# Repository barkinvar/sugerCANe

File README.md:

# sugarCANe — sensor inputs over CAN

[GitHub repository: barkinvar/sugerCANe](https://github.com/barkinvar/sugerCANe)

A compact interface for **three NPN, PNP or logic sensors** on an FRC robot. Each port has a removable **5 V / 12 V power jumper**; input type is configured in software. CAN provides sensor readings, device-ID changes and recoverable firmware updates.

**sugarCANe** is the product name; SC12 Rev H remains the hardware identity. A tiny pixel-cane island sits on the front, below the upper-left mounting hole and above the large capacitor. A vertical pixel wordmark reads bottom to top beside C1. The underside has 79 SMT parts, a small wordmark and TERM/GND service labels. [Front render](current/output/review/board_top.png) · [bottom render](current/output/review/board_bottom.png).

**Isolated compact layout branch (`codex/compact-board`); power transient screening passes; factory qualification remains pending.**

**Start with [Rev H in `current/`](current/README.md).** It is an unbuilt engineering prototype, with [physical qualification still pending](current/docs/VALIDATION.md). It uses its own protocol and drivers; it is not compatible with CTRE Phoenix or GrappleHook.

Rev H adds one RGB status LED on the right, with space for a printed light duct, and a recessed female programming socket for small batches. It retains G's protected sensor supplies, CAN fault reset and rail measurements. See [the engineering review](current/docs/ORDER_READINESS.md) for the evidence and remaining physical tests.

**Selected assembly plan:** JLC fits **129 SMT parts (50 top / 79 bottom)**. You buy **STM32F042K6T6 from DigiKey** and solder U5, then fit ten through-hole parts and three jumper caps. U5 is omitted from the factory BOM, CPL and stencil. The retained dated sourcing snapshot lists stock for ten boards for all 54 factory types; power transient screening passes; factory quotation remains pending. **[Start here: where to buy and how to order](current/docs/FACTORY_ORDER.md).**

| Current design | Detail |
|---|---|
| Board input | 6–22 V DC |
| Sensor power | Regulated 5 V / 12 V; 300 mA shared per rail |
| Supply protection | Current limiting for shorts to ground; **5 V-to-12 V cross-connections are unsupported** |
| Signals | Positive 0–30 V targets; NPN / PNP / push-pull / floating detection / keeper |
| Size and assembly | 44 × 48 mm, four copper layers; **61 fitted parts on top / 79 underneath** |
| User assembly | DigiKey MCU, six terminals, three voltage headers, service socket and three caps |
| Parts estimate | **$27.08 per board at 10 boards** before SMT attrition; **$27.96** with conservative allowance |
| Cost exclusions | PCB, assembly, freight, tax and testing; no factory quotation yet |

The selected purchasing estimate is $2.54 lower per board than the preceding $28.99 estimate, before SMT attrition. It includes the DigiKey MCU; optional spares are extra. Assembly and the reusable programmer are separate. [Cost basis](current/docs/COST_REDUCTION.md).

## Find what you need

| Task | Link |
|---|---|
| Connect and configure sensors | [Wiring](current/docs/WIRING.md) · [input modes](current/docs/INPUT_MODES.md) |
| Understand the power circuit | [Circuit explanation](current/DESIGN_PLAN.md) · [schematic PDF](current/output/assembly/schematic.pdf) |
| Assemble or request a quote | [Factory instructions](current/docs/FACTORY_ORDER.md) · [package status](current/order/README.md) |
| Read LED / choose a programmer | [Status and programming](current/docs/STATUS_AND_PROGRAMMING.md) |
| Program or update over CAN | [CAN service](current/docs/CAN_SERVICE.md) · [robot drivers](current/examples/README.md) |
| Review CAD and tests | [Current design](current/README.md) · [power simulations](current/docs/VALIDATION.md#manufacturer-model-transient-screen) · [validation summary](current/reports/release_checks.json) |
| Download the full design | [Rev H source/release status](current/release/README.md) |

## Why the revisions differ

| Revision | Made for | Main difference |
|---|---|---|
| A | Original four-input concept | 96 × 96 mm baseline |
| B | Smaller, configurable three-input board | 60 × 68 mm; physical power/bias/threshold settings |
| B2 | Factory assembly of B at lower parts cost | Equivalent passives and sourcing; same B circuit |
| C Lite | Simpler, smaller digital interface | 52 × 56 mm; 5 V and protected battery power; fewer parts |
| D SC12 | Industrial sensors needing regulated 12 V | 52 × 64 mm; regulated 5 V / 12 V and rail-health reporting |
| D2 SC12 | Lower-cost assembly and CAN servicing | Hand-fitted terminals, removable voltage jumpers, CAN setup/update |
| E SC12 | Mixed sensor types without bias solder settings | Software NPN/PNP/push-pull/float/keeper; 52 × 70 mm |
| F SC12 | Keep E's features at lower cost | Input-protected boost, cheaper passives; startup/short findings remain in the archive |
| G SC12 | Resolve the power-path findings and enable CAN recovery | Output eFuse, controlled inrush, rail ADCs, default-off enables; 52 × 74 mm |
| **H SC12 — current** | **Visible diagnostics and inexpensive programming for ten boards** | **One RGB LED, buffered data, ordinary 2.54 mm service header; compact branch: 44 × 48 mm, assembly on both sides** |

[Revision details](REVISIONS.md) · [Historical downloads](archive/README.md). Use hardware, firmware and instructions from the same revision.

## Folder map

Clone the repository and enter the maintained design:

```sh
git clone https://github.com/barkinvar/sugerCANe.git
cd sugerCANe/current
```

See [tools and reproduction](current/TOOLS.md) for setup and build instructions.

```text
current/                 The maintained Rev H design
  hardware/              Native KiCad, local libraries and circuit model
  firmware/              MCU application, bootloader and tests
  host/ + examples/      CAN setup tools and robot drivers
  bom/ + order/          Parts lists and factory package status
  docs/                  Wiring, assembly, servicing and qualification
  output/ + reports/     Fabrication exports, drawings and check evidence
  scripts/ + tools/      Reproduction scripts and pinned dependencies
  release/               Release package status
archive/                 Original older release/order ZIPs and checksums
```

Earlier expanded project copies and unused experiments were removed from the current tree. Historical packages are unchanged, and previous sources remain in Git history. [Contributing and generated-file policy](CONTRIBUTING.md).

This branch contains the [compact **44 × 48 mm layout**](current/docs/COMPACT_BOARD.md), using **45.1% less area** than the original 52 × 74 mm board. All 140 fitted parts and electrical functions remain. The mounting holes, connectors and LED move to fit the smaller outline; use the updated mechanical drawings. See [routing checks](current/reports/routing_rules.json) and [all four copper layers](current/output/assembly/gerber_copper_review.pdf). [Size comparison](current/output/review/size_comparison.png).

Ordering update: **0.30 mm minimum via holes, 1 oz outer / 0.5 oz inner copper**, and corrected CPL coordinates matching the Gerber origin. All component positions and trace geometry are retained. Re-upload the matching Gerber ZIP and CPL together. [Checks and order settings](current/docs/FABRICATION_OPTIONS.md).

The input connector-to-fuse and fuse-to-MOSFET routes are now **0.7 mm wide** (14 segments widened from 0.5 mm). The protected input and converter paths retain their reviewed clearance necks. Width, clearance, connectivity and ground-pour checks cover **all four layers**; see the [power-path review](current/docs/ORDER_READINESS.md).

| Copper layer | Role | PNG | SVG |
|---|---|---|---|
| Top | Components, signals and power | [PNG](current/output/review/gerber_top_copper.png) | [SVG](current/output/review/gerber_top_copper.svg) |
| Inner 1 | Ground plane | [PNG](current/output/review/gerber_inner_1_copper.png) | [SVG](current/output/review/gerber_inner_1_copper.svg) |
| Inner 2 | Ground with selected signals and low-current supply branches | [PNG](current/output/review/gerber_inner_2_copper.png) | [SVG](current/output/review/gerber_inner_2_copper.svg) |
| Bottom | Signals, power and ground | [PNG](current/output/review/gerber_bottom_copper.png) | [SVG](current/output/review/gerber_bottom_copper.svg) |

These views show the actual exported copper and drills. Inner layers are viewed from the top; the bottom is mirrored for an underside view.

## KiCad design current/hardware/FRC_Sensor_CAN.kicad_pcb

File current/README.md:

# sugarCANe / SC12 Rev H — current design

[Repository: barkinvar/sugerCANe](https://github.com/barkinvar/sugerCANe) · [Folder map](../README.md#folder-map)

Three digital sensor inputs over CAN, with regulated **5 V / 12 V sensor power** and software-selectable **NPN, PNP, push-pull, floating detection and keeper**. Removable 2 mm jumpers select each port's power voltage. Components populate both PCB surfaces.

A tiny pixel-cane island sits on the front, below the upper-left mounting hole and above C1. A vertical pixel wordmark reads bottom to top beside C1. The underside carries 79 fitted SMT parts, a compact sugarCANe wordmark, and labels for the termination bridge and ground test pad. Connector and voltage labels remain on top; the programming map is in the wiring guide. [Bottom render](output/review/board_bottom.png).

Rev H adds one enclosure-facing RGB status LED and a hand-soldered recessed female programming socket for a ten-board batch. The LED is on the right, above the mounting hole, with a 6 mm circular area reserved for a printed light duct; see the [enclosure dimensions](docs/STATUS_AND_PROGRAMMING.md#enclosure-location). It retains Rev G's power protection and physical voltage jumpers. The 12 V reservoir is upstream of a controlled output eFuse; both rails have default-off enables and CAN fault reset. Two ADC channels measure the protected rails. [Engineering review](docs/ORDER_READINESS.md) · [verification and bench procedure](docs/VALIDATION.md). This design uses its own CAN protocol; it is not CTRE Phoenix or GrappleHook compatible.

**Selected assembly plan:** JLC fits **129 SMT parts (50 top / 79 bottom)**. You buy **STM32F042K6T6 from DigiKey** and solder U5, then fit ten through-hole parts and three jumper caps. U5 is omitted from the factory BOM, CPL and stencil. The retained dated sourcing snapshot lists stock for ten boards for all 54 factory types; power transient screening passes; factory quotation remains pending. **[Start here: where to buy and how to order](docs/FACTORY_ORDER.md).**

| Specification | Rev H |
|---|---|
| Board supply | 6–22 V DC |
| Sensor supplies | Regulated 5 V / 12 V; **300 mA shared per rail**, not per port |
| Signal targets | Positive 0–30 V; LOW ≤1.2 V, HIGH ≥2.4 V; common ground |
| Input setup | Software bias and active-state selection independently per channel |
| Protection | Reverse input, fuse/TVS, separate protected 5 V and 12 V outputs, controlled 12 V inrush |
| Fault reset | Remove the fault, then use CAN power reset; hardware limits remain independent |
| Controller | STM32F042K6T6, TCAN3413; 1 Mbit/s classic CAN |
| Software | App 0.9.0, bootloader 1.1.0, hardware 8, protocol 4 |
| Servicing | CAN discovery, ID/settings and recoverable firmware upload; initial installation through a 2.54 mm SWD service socket |
| PCB / assembly | **44 × 48 mm**, four copper layers, 129 factory SMT + user-fitted MCU + ten through-hole parts + three caps |

Parts purchasing is about **$27.08 per board at ten boards before SMT attrition**, or **$27.96** including a conservative allowance. These include the user-fitted DigiKey MCU, through-hole parts and caps; two optional spare MCUs are extra. PCB, assembly, freight and tax are extra. [Cost calculation](docs/COST_REDUCTION.md).

| What you want to do | Start here |
|---|---|
| Wire and configure a sensor | [Wiring](docs/WIRING.md), [input modes](docs/INPUT_MODES.md) |
| Understand the circuit | [Power and input design](DESIGN_PLAN.md), [schematic PDF](output/assembly/schematic.pdf) |
| Request a prototype quotation | [Factory instructions](docs/FACTORY_ORDER.md), [package status](order/README.md) |
| Read LED / choose a programmer | [Status and programming](docs/STATUS_AND_PROGRAMMING.md) |
| Assemble and program | [Assembly](docs/ASSEMBLY.md), [unit fixture](docs/FIXTURE.md), [CAN service](docs/CAN_SERVICE.md) |
| Write robot code | [Examples/drivers](examples/README.md), [CAN protocol](docs/CAN_PROTOCOL.md) |
| Edit the board | [KiCad project](hardware/FRC_Sensor_CAN.kicad_pro), [PCB](hardware/FRC_Sensor_CAN.kicad_pcb), [interactive BOM](output/assembly/interactive_bom.html) |
| Design an enclosure | [STEP](output/mechanical/FRC_Sensor_CAN.step), [mechanical drawing](output/mechanical/mechanical_drawing.pdf) |
| Review or reproduce checks | [Validation](docs/VALIDATION.md), [power simulations](reports/electrical/boost_spice.json), [check summary](reports/release_checks.json), [tool setup](TOOLS.md) |
| Download everything | [Source/release status](release/README.md), [handbook](output/documentation/SC12_RevH_Handbook.pdf) |

Change voltage jumpers only with power disconnected. A missing cap disconnects port power, not its signal wire. Input mode changes use CAN software. Rail voltage readback uses the MCU ADC and factory voltage-reference calibration. External signal inputs remain digital; rail measurement does not add user analog-input or encoder support.

The compact variant is **44 × 48 mm**, using **45.1% less area** than the original 52 × 74 mm board. It retains all 140 fitted parts and electrical functions, with 79 parts underneath. Mounting holes, connectors and the LED move to suit the smaller outline. See the [compact layout review](docs/COMPACT_BOARD.md), [routing checks](reports/routing_rules.json), [all four copper layers](output/assembly/gerber_copper_review.pdf) and [connector details](docs/CONNECTORS.md). [Size comparison](output/review/size_comparison.png).

Ordering update: **0.30 mm minimum via holes, 1 oz outer / 0.5 oz inner copper**, and corrected CPL coordinates matching the Gerber origin. All component positions and trace geometry are retained. Re-upload the matching Gerber ZIP and CPL together. [Checks and order settings](docs/FABRICATION_OPTIONS.md).

The input connector-to-fuse and fuse-to-MOSFET routes are now **0.7 mm wide** (14 segments widened from 0.5 mm). The protected input and converter paths retain their reviewed clearance necks. Width, clearance, connectivity and ground-pour checks cover **all four layers**; see the [power-path review](docs/ORDER_READINESS.md).

| Copper layer | Role | PNG | SVG |
|---|---|---|---|
| Top | Components, signals and power | [PNG](output/review/gerber_top_copper.png) | [SVG](output/review/gerber_top_copper.svg) |
| Inner 1 | Ground plane | [PNG](output/review/gerber_inner_1_copper.png) | [SVG](output/review/gerber_inner_1_copper.svg) |
| Inner 2 | Ground with selected signals and low-current supply branches | [PNG](output/review/gerber_inner_2_copper.png) | [SVG](output/review/gerber_inner_2_copper.svg) |
| Bottom | Signals, power and ground | [PNG](output/review/gerber_bottom_copper.png) | [SVG](output/review/gerber_bottom_copper.svg) |

These views show the actual exported copper and drills. Inner layers are viewed from the top; the bottom is mirrored for an underside view.

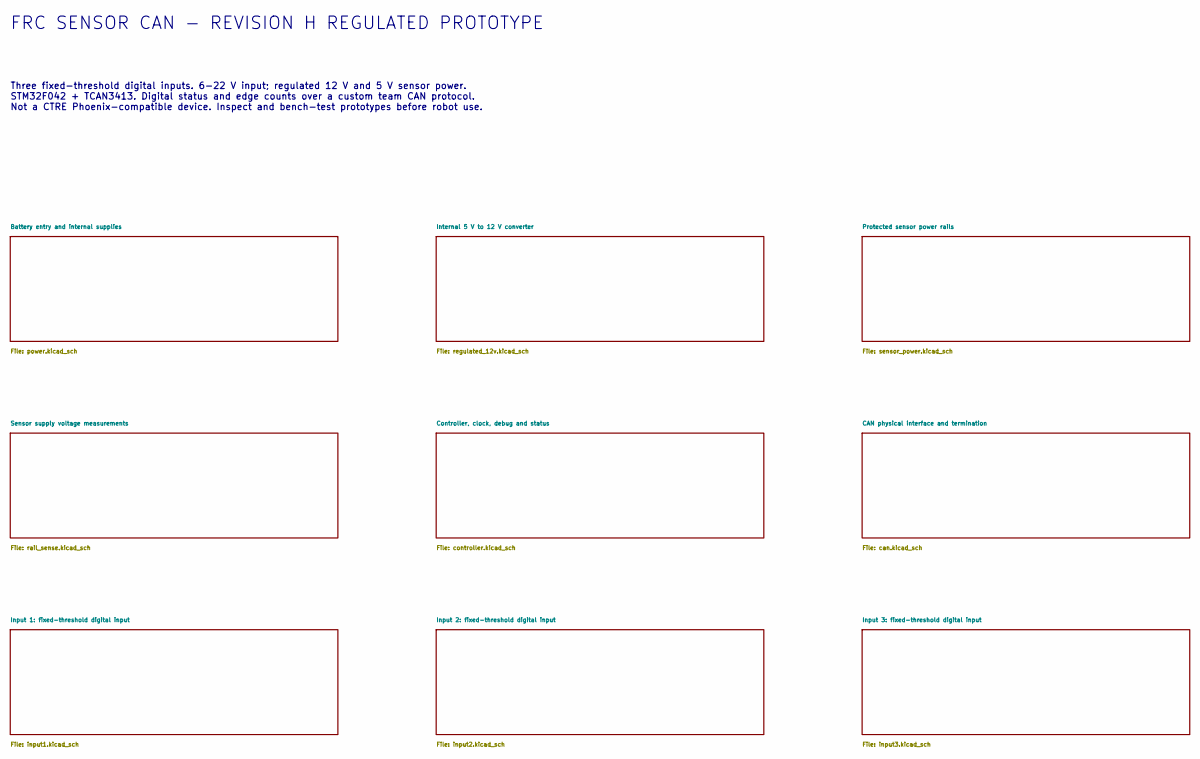
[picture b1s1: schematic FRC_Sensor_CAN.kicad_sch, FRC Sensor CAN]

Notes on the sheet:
FRC SENSOR CAN - REVISION H REGULATED PROTOTYPE
Three fixed-threshold digital inputs. 6-22 V input; regulated 12 V and 5 V sensor power. STM32F042 + TCAN3413. Digital status and edge counts over a custom team CAN protocol. Not a CTRE Phoenix-compatible device. Inspect and bench-test prototypes before robot use.

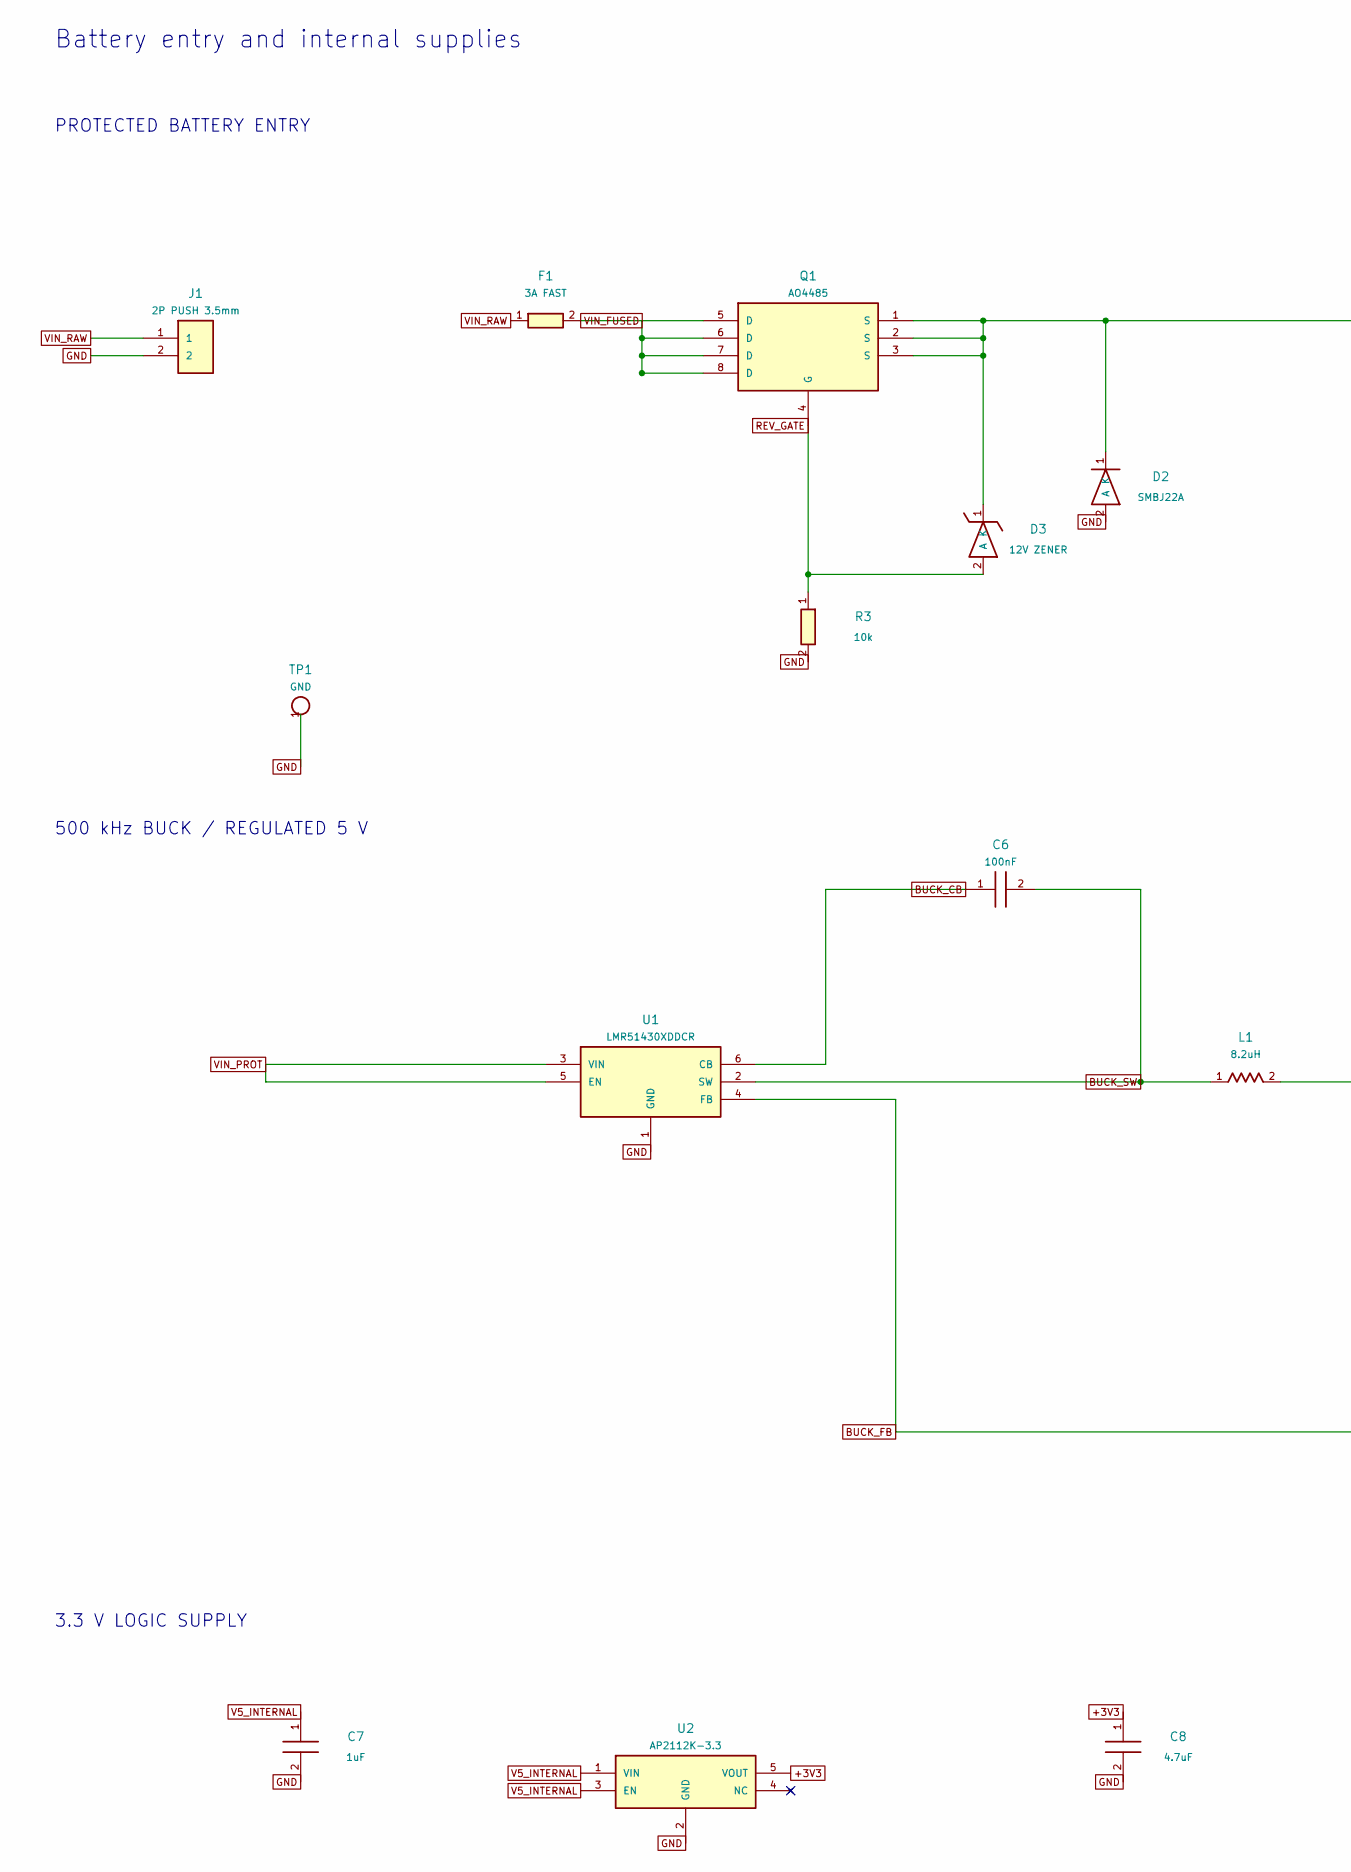
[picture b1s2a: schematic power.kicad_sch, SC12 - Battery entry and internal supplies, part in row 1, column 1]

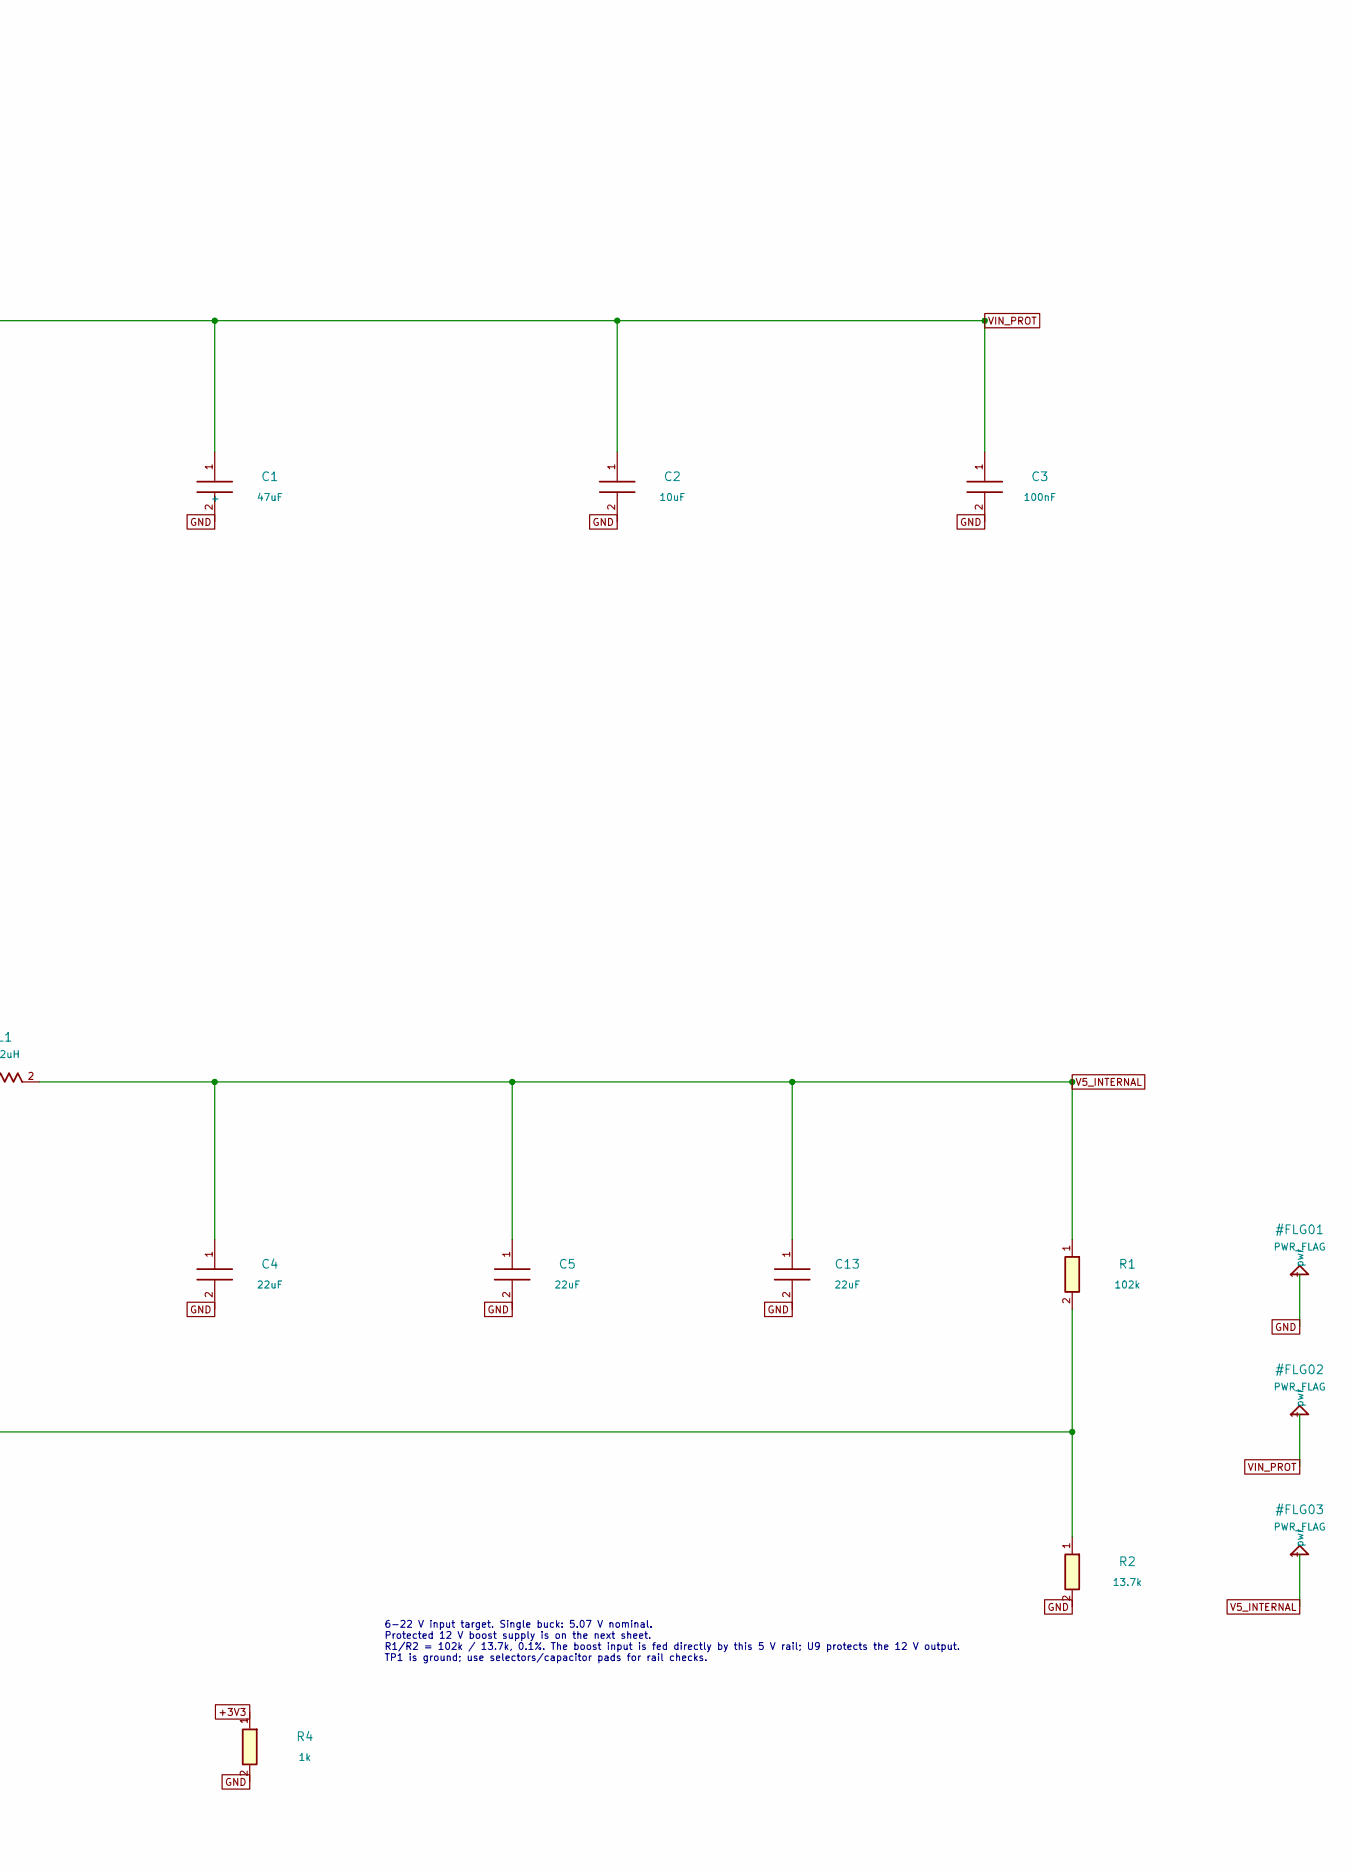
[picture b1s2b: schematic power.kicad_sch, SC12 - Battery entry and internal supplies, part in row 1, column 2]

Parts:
C1: 47uF; CP_Panasonic_FT_6.3x5.8; MPN EEEFT1H470AP
C2: 10uF; C_1210_3225Metric; MPN CL32B106KBJNNWE
C3, C6: 100nF; C_0805_2012Metric; MPN CL21B104KCFNNNE
C4, C5, C13: 22uF; C_1206_3216Metric; MPN CL31A226KAHNNNE
C7: 1uF; C_0805_2012Metric; MPN CL21B105KBFNNNE
C8: 4.7uF; C_0805_2012Metric; MPN CL21B475KAFNNNE
D2: SMBJ22A; D_SMB; MPN SMBJ22A-E3/52
D3: 12V ZENER; D_SOD-123; MPN MMSZ12T1G
F1: 3A FAST; Fuse_Littelfuse-NANO2-451_453; MPN 0451003.MRL
J1: 2P PUSH 3.5mm; Weidmuller_LSF_90_2P; MPN 1824420000
L1: 8.2uH; L_Bourns_SRP7028A_7.3x6.6mm; MPN SRP7028A-8R2M
Q1: AO4485; SOIC-8_3.9x4.9mm_P1.27mm; MPN AO4485
R1: 102k; R_0805_2012Metric; MPN RT0805BRD07102KL
R2: 13.7k; R_0805_2012Metric; MPN RT0805BRD0713K7L
R3: 10k; R_0805_2012Metric; MPN 0805W8F1002T5E
R4: 1k; R_0805_2012Metric; MPN 0805W8F1001T5E
TP1: GND; TestPoint_Pad_D2.0mm
U1: LMR51430XDDCR; TSOT-23-6; MPN LMR51430XDDCR
U2: AP2112K-3.3; SOT-23-5; MPN AP2112K-3.3TRG1

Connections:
+3V3: C8.1, R4.1, U2.5 (VOUT); also elsewhere on the board
BUCK_CB: C6.1, U1.6 (CB)
BUCK_FB: R1.2, R2.1, U1.4 (FB)
BUCK_SW: C6.2, L1.1, U1.2 (SW)
GND: C1.2, C2.2, C3.2, C4.2, C5.2, C7.2, C8.2, C13.2, D2.2 (A), J1.2, R2.2, R3.2, R4.2, TP1.1, U1.1 (GND), U2.2 (GND); also elsewhere on the board
REV_GATE: D3.2 (A), Q1.4 (G), R3.1
V5_INTERNAL: C4.1, C5.1, C7.1, C13.1, L1.2, R1.1, U2.1 (VIN), U2.3 (EN); also elsewhere on the board
VIN_FUSED: F1.2, Q1.5 (D), Q1.6 (D), Q1.7 (D), Q1.8 (D)
VIN_PROT: C1.1 (+), C2.1, C3.1, D2.1 (K), D3.1 (K), Q1.1 (S), Q1.2 (S), Q1.3 (S), U1.3 (VIN), U1.5 (EN)
VIN_RAW: F1.1, J1.1

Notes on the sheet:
Battery entry and internal supplies
PROTECTED BATTERY ENTRY
500 kHz BUCK / REGULATED 5 V
3.3 V LOGIC SUPPLY
6-22 V input target. Single buck: 5.07 V nominal. Protected 12 V boost supply is on the next sheet. R1/R2 = 102k / 13.7k, 0.1%. The boost input is fed directly by this 5 V rail; U9 protects the 12 V output. TP1 is ground; use selectors/capacitor pads for rail checks.

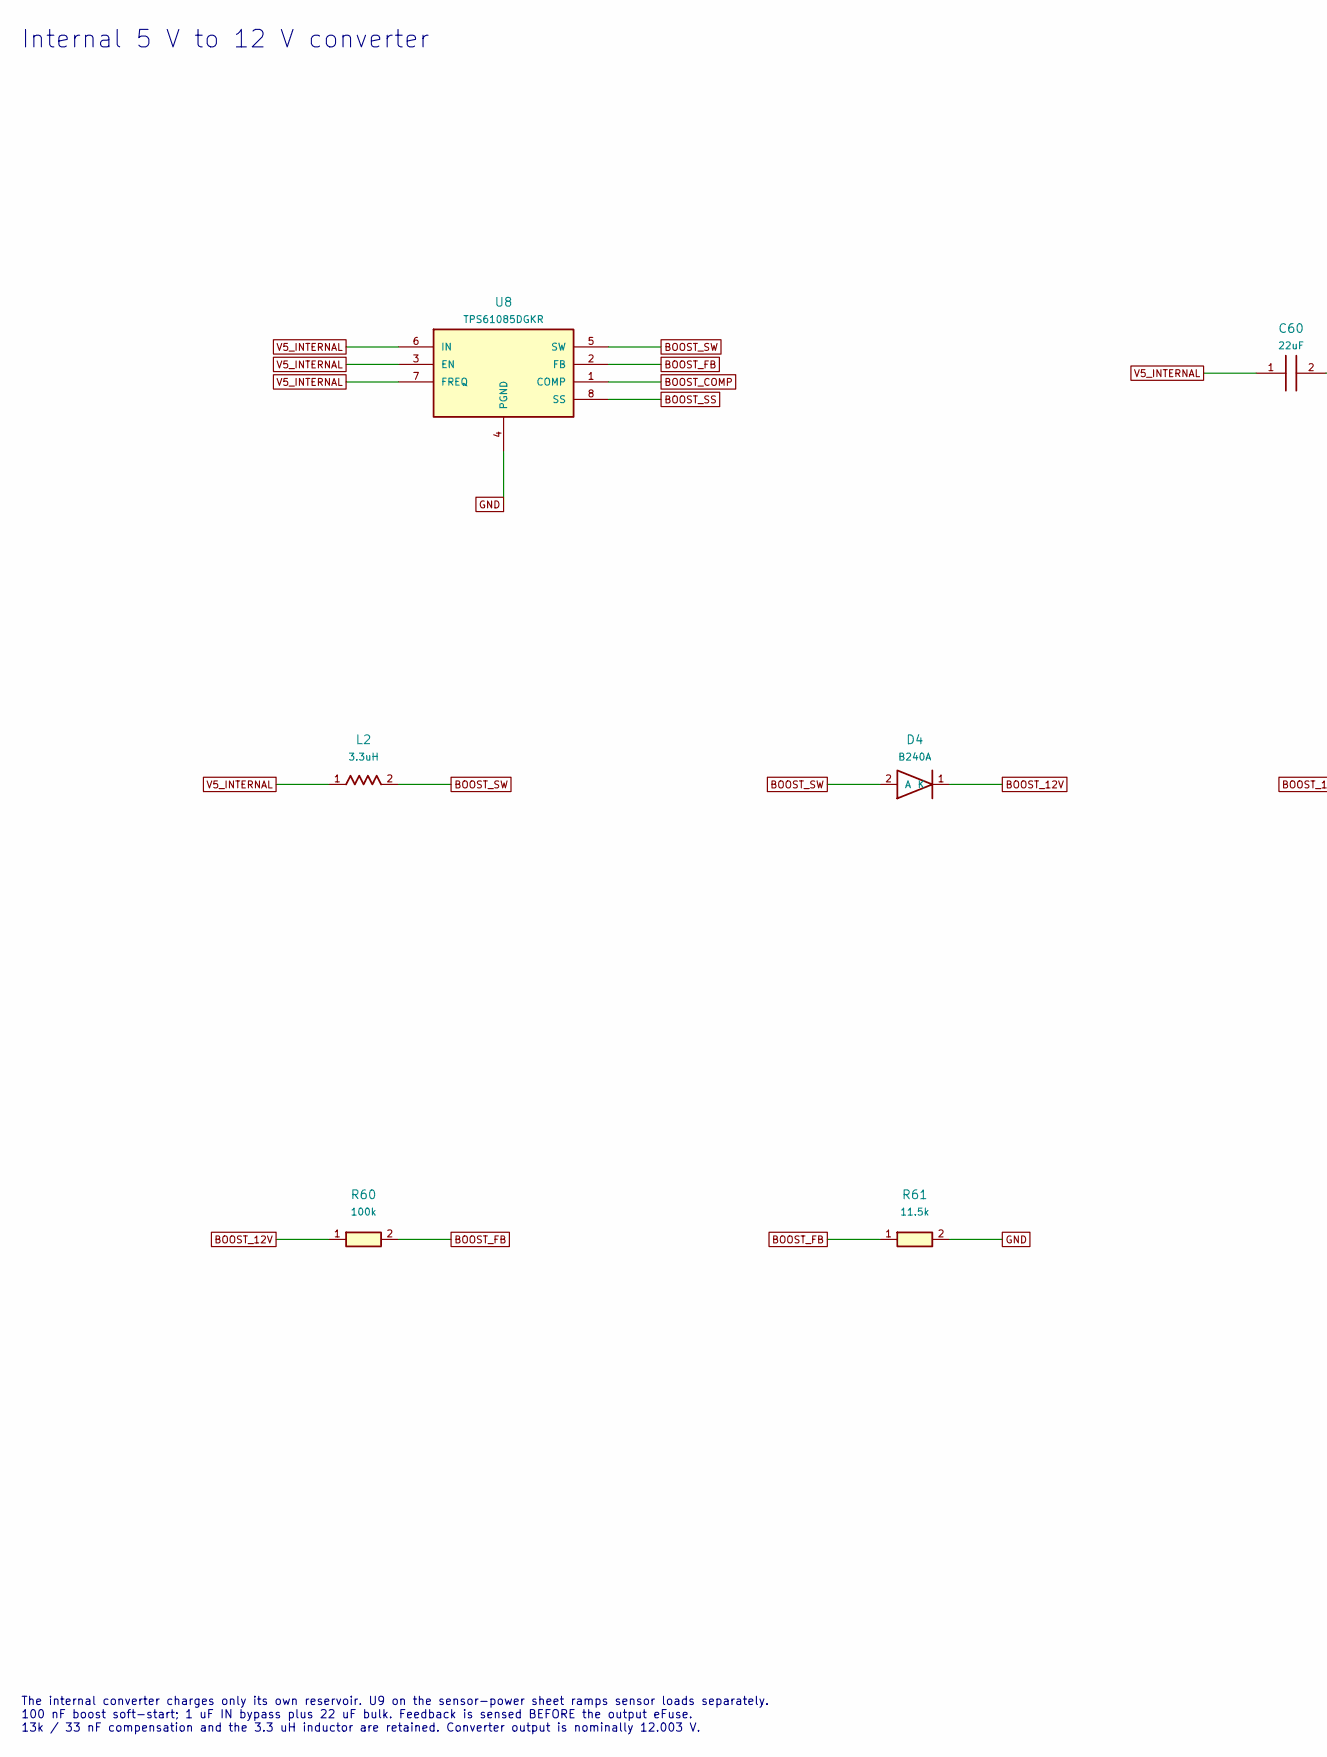
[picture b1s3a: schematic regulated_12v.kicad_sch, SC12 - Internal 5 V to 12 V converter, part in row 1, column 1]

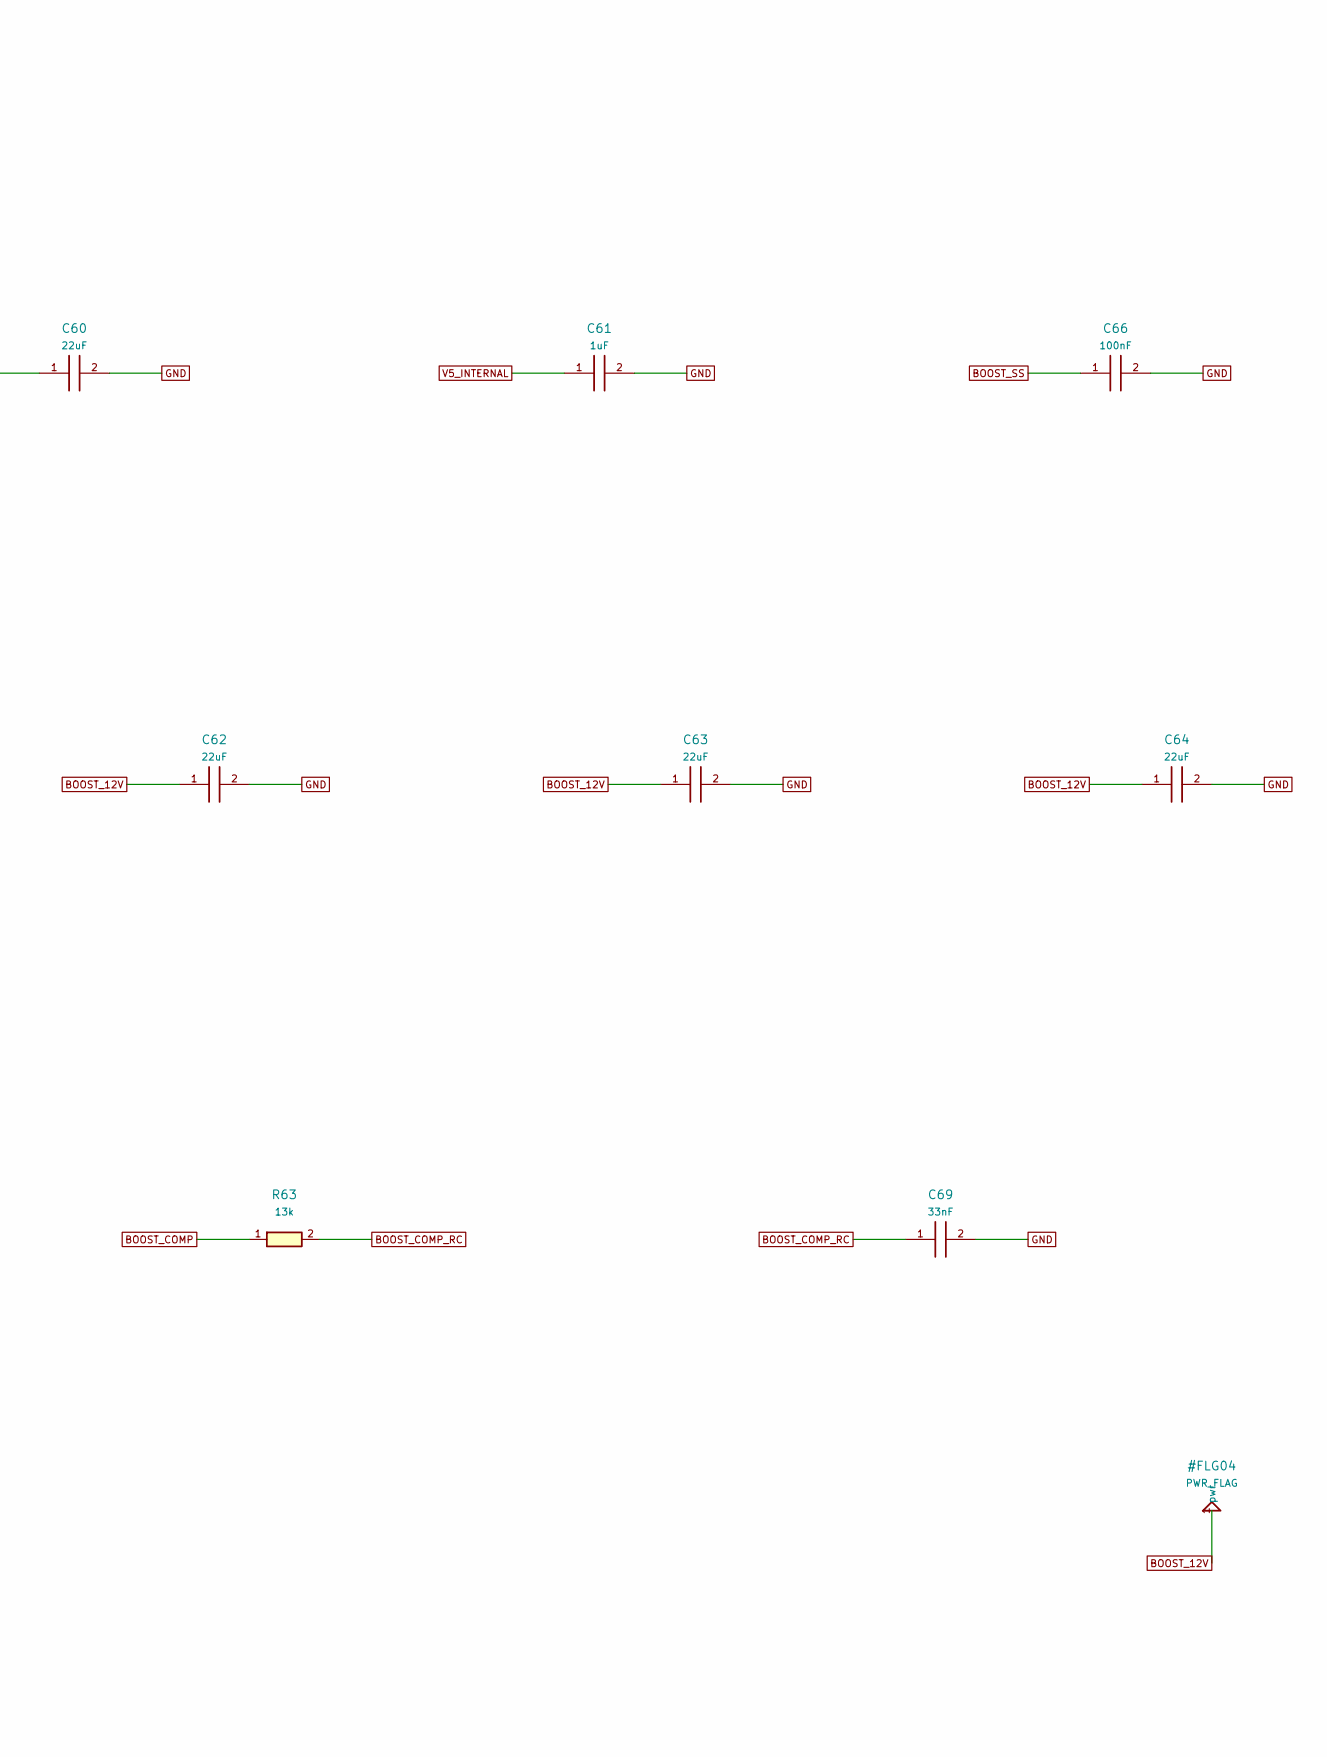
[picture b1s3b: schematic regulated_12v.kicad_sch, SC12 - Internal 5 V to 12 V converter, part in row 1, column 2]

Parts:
C60, C62, C63, C64: 22uF; C_1206_3216Metric; MPN CL31A226KAHNNNE
C61: 1uF; C_0805_2012Metric; MPN CL21B105KBFNNNE
C66: 100nF; C_0805_2012Metric; MPN CL21B104KCFNNNE
C69: 33nF; C_0805_2012Metric; MPN CC0805KRX7R9BB333
D4: B240A; D_SMA; MPN B240A-13-F
L2: 3.3uH; L_Bourns_SRP5030T; MPN SRP5030TA-3R3M
R60: 100k; R_0805_2012Metric; MPN RT0805BRD07100KL
R61: 11.5k; R_0805_2012Metric; MPN 0805W8F1152T5E
R63: 13k; R_0805_2012Metric; MPN RC0805FR-0713KL
U8: TPS61085DGKR; VSSOP-8_3x3mm_P0.65mm; MPN TPS61085DGKR

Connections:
BOOST_12V: C62.1, C63.1, C64.1, D4.1 (K), R60.1; also elsewhere on the board
BOOST_COMP: R63.1, U8.1 (COMP)
BOOST_COMP_RC: C69.1, R63.2
BOOST_FB: R60.2, R61.1, U8.2 (FB)
BOOST_SS: C66.1, U8.8 (SS)
BOOST_SW: D4.2 (A), L2.2, U8.5 (SW)
GND: C60.2, C61.2, C62.2, C63.2, C64.2, C66.2, C69.2, R61.2, U8.4 (PGND); also elsewhere on the board
V5_INTERNAL: C60.1, C61.1, L2.1, U8.3 (EN), U8.6 (IN), U8.7 (FREQ); also elsewhere on the board

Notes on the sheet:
Internal 5 V to 12 V converter
The internal converter charges only its own reservoir. U9 on the sensor-power sheet ramps sensor loads separately. 100 nF boost soft-start; 1 uF IN bypass plus 22 uF bulk. Feedback is sensed BEFORE the output eFuse. 13k / 33 nF compensation and the 3.3 uH inductor are retained. Converter output is 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
